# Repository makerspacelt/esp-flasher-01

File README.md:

This is ESP-01 interface to connect with the [esp-flasher](http://esp-flasher.makerspace.lt/repo).

Support this open-source project - buy your fully assembled and tested device [here](http://esp-01.makerspace.lt/shop)

Dev NOTE: before commit, run `./kibot.sh` to regenerate documentation, gerbers and other assets.

* [schematics.pdf](gen/schematics.pdf)
* [pcb.pdf with dimensions](gen/pcb.pdf)

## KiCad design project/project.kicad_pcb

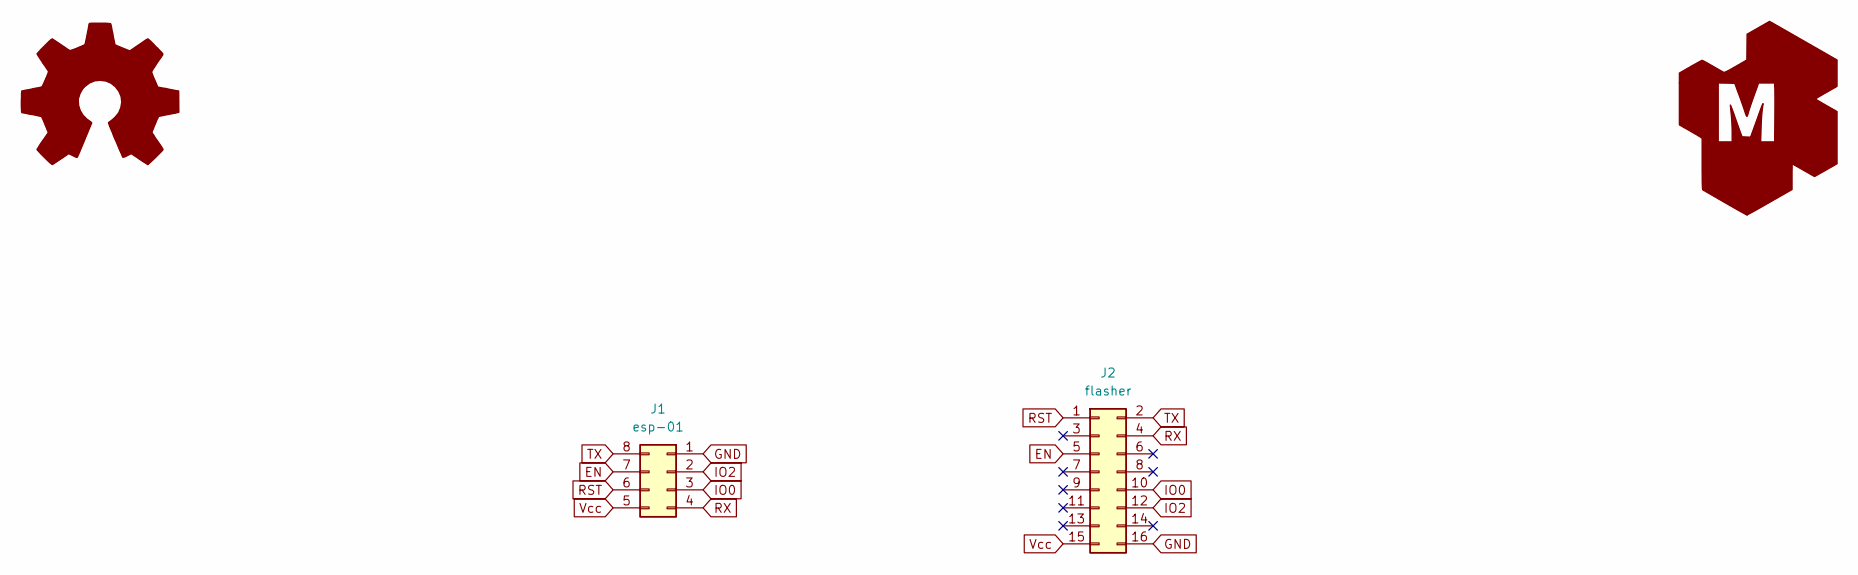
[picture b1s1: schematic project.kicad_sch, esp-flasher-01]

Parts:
G1: Logo_Open_Hardware_Large; OSHW-Symbol_6.7x6mm_SilkScreen
G2: LOGO_KMS; logo_kms_small_silkscreen
J1: esp-01; PinSocket_2x04_P2.54mm_Vertical; jlc-part-type E
J2: flasher; IDC-Header_2x08_P2.54mm_Vertical; jlc-part-type E

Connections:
EN: J1.7, J2.5
GND: J1.1, J2.16
IO0: J1.3, J2.10
IO2: J1.2, J2.12
RST: J1.6, J2.1
RX: J1.4, J2.4
TX: J1.8, J2.2
Vcc: J1.5, J2.15

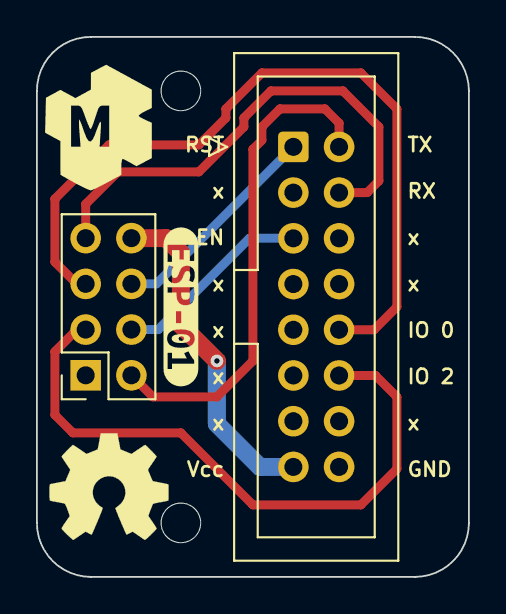
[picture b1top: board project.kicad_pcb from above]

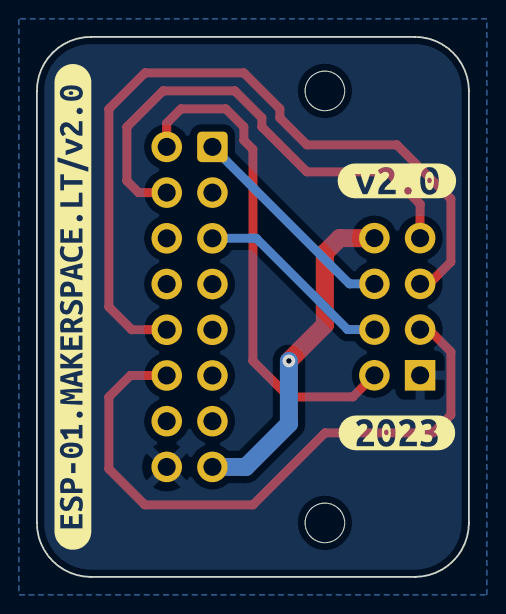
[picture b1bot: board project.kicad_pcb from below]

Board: 2 copper layers, 24.0 x 30.0 mm, 8 parts (3 on the bottom side), 8 nets.

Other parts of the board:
kibuzzard-642C03EC: G***; kibuzzard-642C03EC
kibuzzard-642C03F5: G***; kibuzzard-642C03F5
kibuzzard-64333B2E: G***; kibuzzard-64333B2E
kibuzzard-643343D4: G***; kibuzzard-643343D4

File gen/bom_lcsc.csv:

"Quantity","LCSC Part Number","Value","Footprint"
"1","C92271","esp-01","PinSocket_2x04_P2.54mm_Vertical"
"1","C3406","flasher","IDC-Header_2x08_P2.54mm_Vertical"

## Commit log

2023-05-12 adding real project photo
2023-05-12 fixing image filename in readme
2023-05-20 adding CERN-OHL-S v2 license
